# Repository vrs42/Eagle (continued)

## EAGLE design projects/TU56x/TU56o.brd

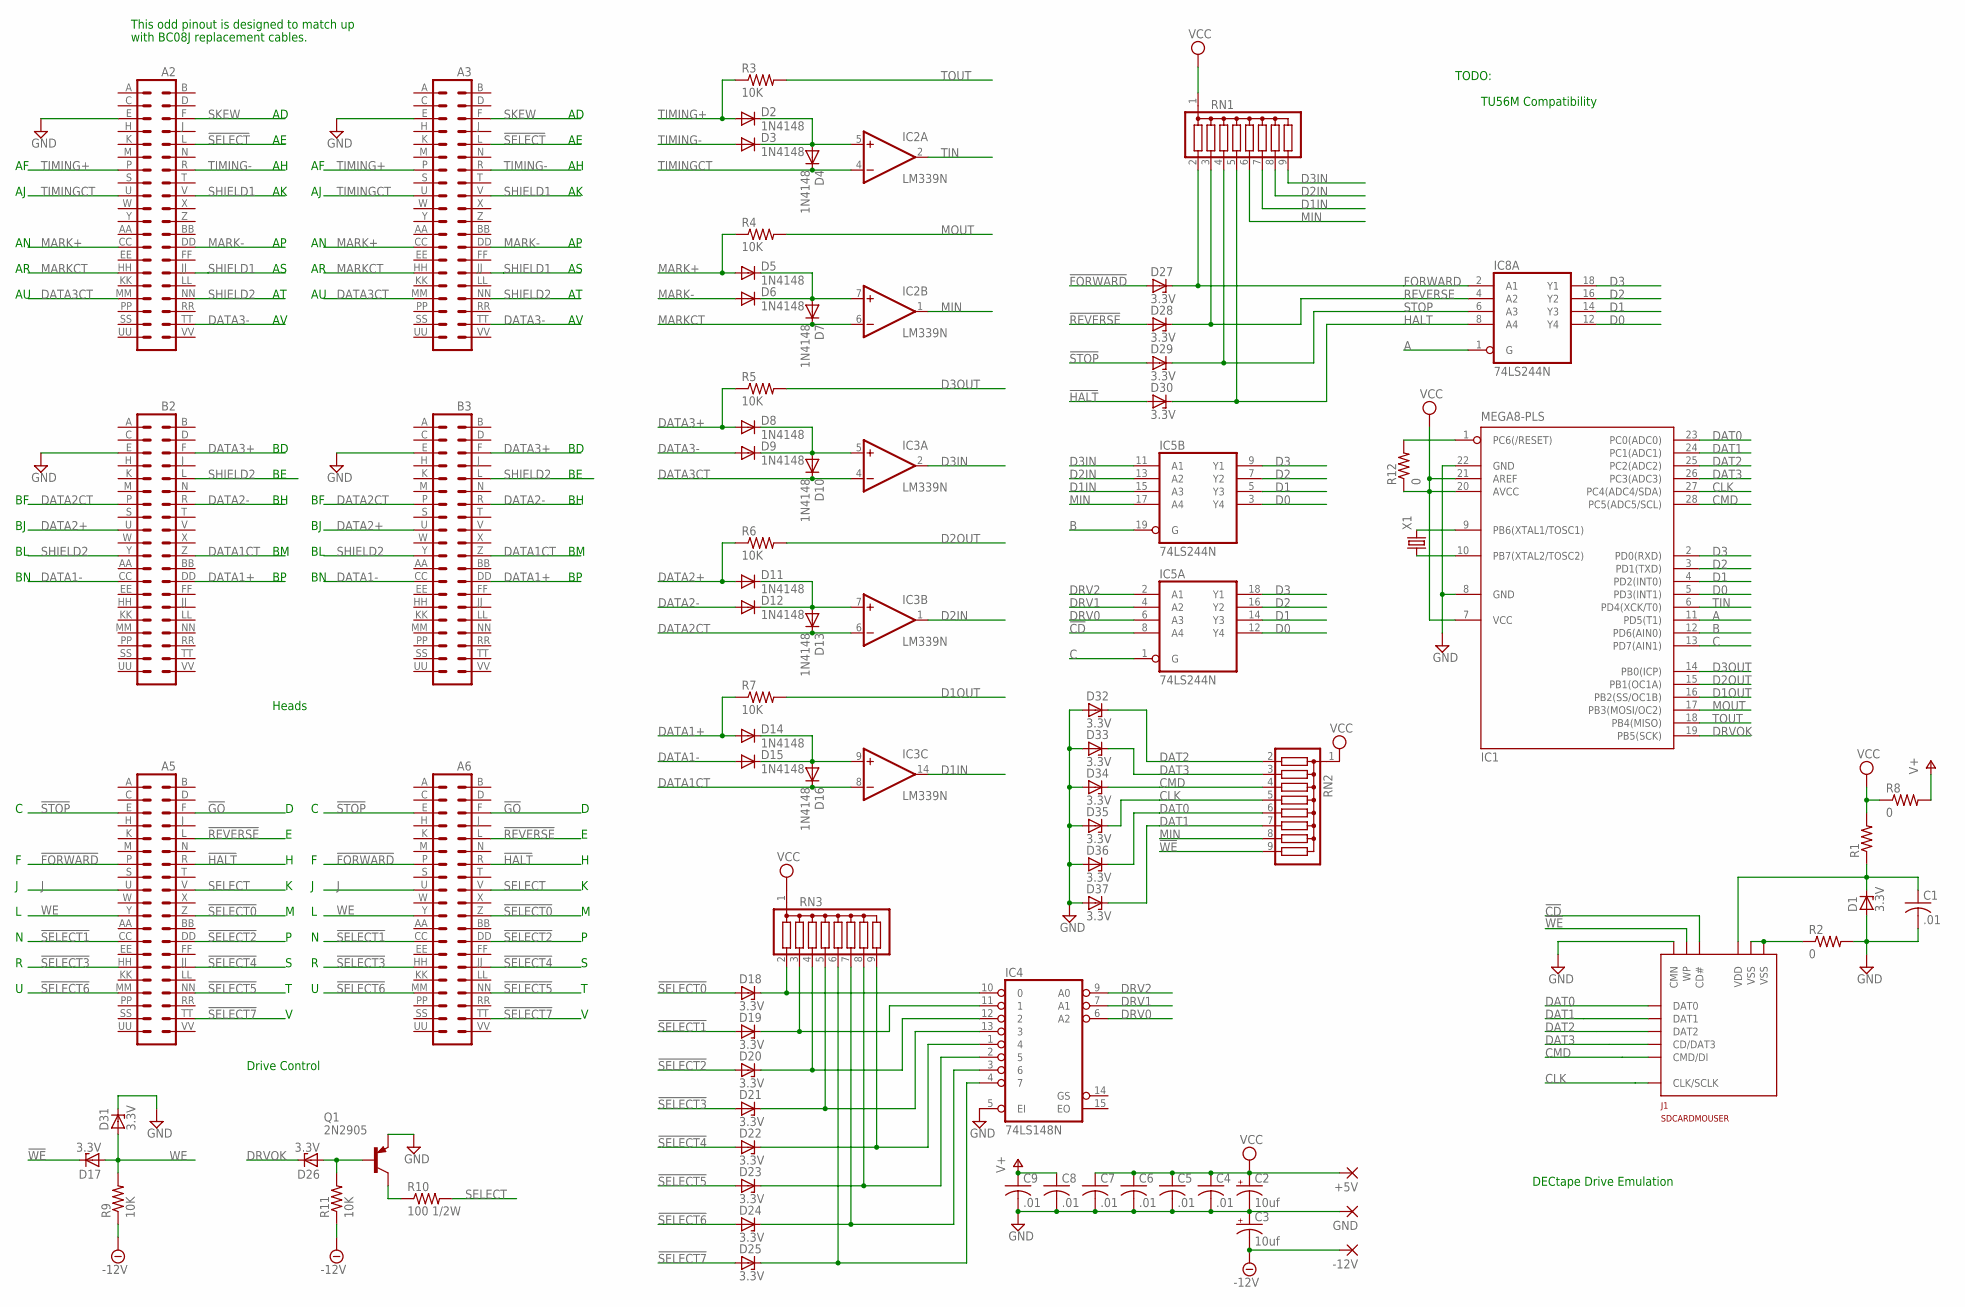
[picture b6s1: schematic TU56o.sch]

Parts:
+5V: 2,15/1,0
-12V: 2,15/1,0
A2, A3, A5, A6: DEC40PINV
B2, B3: DEC40PINV
C1, C4, C5, C6, C7, C8, C9: .01; C050-025X075
C2, C3: 10uf; E2,5-7
D1, D17, D18, D19, D20, D21, D22, D23, D24, D25, D26, D27, D28, D29, D30, D31, D32, D33, D34, D35, D36, D37: 3.3V; DO35Z10
D2, D3, D4, D5, D6, D7, D8, D9, D10, D11, D12, D13, D14, D15, D16: 1N4148; DO35-10
GND: 2,15/1,0
IC1: MEGA8-PLS; DIL28-3
IC2, IC3: LM339N; DIL14
IC4: 74LS148N; DIL16
IC5, IC8: 74LS244N; DIL20
J1: SDCARDMOUSER; SCDA1A
Q1: 2N2905; TO5
R1: R-US_0207/10; 0207/10
R2, R8, R12: 0; 0207/10
R3, R4, R5, R6, R7, R9, R11: 10K; 0207/10
R10: 100 1/2W; 0309V
RN1, RN2, RN3: G08R; SIL9
X1: CRYSTALHC49S; HC49/S

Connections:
!CD: IC5.8 (A4), J1.10 (CD#)
!FORWARD: A5.P (13), A6.P (13), D27.A
!GO: A5.F (6), A6.F (6)
!HALT: A5.R (14), A6.R (14), D30.A
!REVERSE: A5.L (10), A6.L (10), D28.A
!SELECT: A2.L (10), A3.L (10)
!SELECT0: A5.Z (22), A6.Z (22), D18.A
!SELECT1: A5.CC (25), A6.CC (25), D19.A
!SELECT2: A5.DD (26), A6.DD (26), D20.A
!SELECT3: A5.HH (29), A6.HH (29), D21.A
!SELECT4: A5.JJ (30), A6.JJ (30), D22.A
!SELECT5: A5.NN (34), A6.NN (34), D23.A
!SELECT6: A5.MM (33), A6.MM (33), D24.A
!SELECT7: A5.TT (38), A6.TT (38), D25.A
!STOP: A5.E (5), A6.E (5), D29.A
!WE: D17.C, J1.12 (WP), RN2.9
-12V: -12V.1, C3.-, R9.1, R11.1
A: IC1.11 (PD5(T1)), IC8.1 (G)
B: IC1.12 (PD6(AIN0)), IC5.19 (G)
C: IC1.13 (PD7(AIN1)), IC5.1 (G)
CLK: D35.C, IC1.27 (PC4(ADC4/SDA)), J1.5 (CLK/SCLK), RN2.5
CMD: D34.C, IC1.28 (PC5(ADC5/SCL)), J1.2 (CMD/DI), RN2.4
D0: IC1.5 (PD3(INT1)), IC5.3 (Y4), IC5.12 (Y4), IC8.12 (Y4)
D1: IC1.4 (PD2(INT0)), IC5.5 (Y3), IC5.14 (Y3), IC8.14 (Y3)
D1IN: IC3.14 (OUT), IC5.15 (A3), RN1.7
D1OUT: IC1.16 (PB2(SS/OC1B)), R7.2
D2: IC1.3 (PD1(TXD)), IC5.7 (Y2), IC5.16 (Y2), IC8.16 (Y2)
D2IN: IC3.1 (OUT), IC5.13 (A2), RN1.8
D2OUT: IC1.15 (PB1(OC1A)), R6.2
D3: IC1.2 (PD0(RXD)), IC5.9 (Y1), IC5.18 (Y1), IC8.18 (Y1)
D3IN: IC3.2 (OUT), IC5.11 (A1), RN1.9
D3OUT: IC1.14 (PB0(ICP)), R5.2
DAT0: D36.C, IC1.23 (PC0(ADC0)), J1.7 (DAT0), RN2.6
DAT1: D37.C, IC1.24 (PC1(ADC1)), J1.8 (DAT1), RN2.7
DAT2: D32.C, IC1.25 (PC2(ADC2)), J1.9 (DAT2), RN2.2
DAT3: D33.C, IC1.26 (PC3(ADC3)), J1.1 (CD/DAT3), RN2.3
DATA1+: B2.DD (26), B3.DD (26), D14.A, R7.1
DATA1-: B2.CC (25), B3.CC (25), D15.A
DATA1CT: B2.Z (22), B3.Z (22), D16.C, IC3.8 (-IN)
DATA2+: B2.U (17), B3.U (17), D11.A, R6.1
DATA2-: B2.R (14), B3.R (14), D12.A
DATA2CT: B2.P (13), B3.P (13), D13.C, IC3.6 (-IN)
DATA3+: B2.F (6), B3.F (6), D8.A, R5.1
DATA3-: A2.TT (38), A3.TT (38), D9.A
DATA3CT: A2.MM (33), A3.MM (33), D10.C, IC3.4 (-IN)
DRV0: IC4.6 (A2), IC5.6 (A3)
DRV1: IC4.7 (A1), IC5.4 (A2)
DRV2: IC4.9 (A0), IC5.2 (A1)
DRVOK: D26.C, IC1.19 (PB5(SCK))
FORWARD: D27.C, IC8.2 (A1), RN1.2
GND: A2.E (5), A3.E (5), B2.E (5), B3.E (5), C1.2, C2.-, C3.+, C4.2, C5.2, C6.2, C7.2, C8.2, C9.2, D1.A, D31.C, D32.A, D33.A, D34.A, D35.A, D36.A, D37.A, GND.1, IC1.8 (GND), IC1.22 (GND), IC2.12 (GND), IC3.12 (GND), IC4.5 (EI), IC4.8 (GND), IC5.10 (GND), IC8.10 (GND), J1.11 (CMN), J1.13 (GND), J1.14 (GND), Q1.1 (E), R2.2
HALT: D30.C, IC8.8 (A4), RN1.5
J: A5.U (17), A6.U (17)
MARK+: A2.CC (25), A3.CC (25), D5.A, R4.1
MARK-: A2.DD (26), A3.DD (26), D6.A
MARKCT: A2.HH (29), A3.HH (29), D7.C, IC2.6 (-IN)
MIN: IC2.1 (OUT), IC5.17 (A4), RN1.6, RN2.8
MOUT: IC1.17 (PB3(MOSI/OC2)), R4.2
unnamed: IC1.10 (PB7(XTAL2/TOSC2)), X1.1
unnamed: IC1.9 (PB6(XTAL1/TOSC1)), X1.2
unnamed: D18.C, IC4.10 (0), RN3.2
unnamed: D19.C, IC4.11 (1), RN3.3
unnamed: D20.C, IC4.12 (2), RN3.4
unnamed: D2.C, D3.C, D4.A, IC2.5 (+IN)
unnamed: D21.C, IC4.13 (3), RN3.5
unnamed: D22.C, IC4.1 (4), RN3.9
unnamed: D23.C, IC4.2 (5), RN3.8
unnamed: D5.C, D6.C, D7.A, IC2.7 (+IN)
unnamed: D8.C, D9.C, D10.A, IC3.5 (+IN)
unnamed: D11.C, D12.C, D13.A, IC3.7 (+IN)
unnamed: D14.C, D15.C, D16.A, IC3.9 (+IN)
unnamed: D24.C, IC4.3 (6), RN3.7
unnamed: D25.C, IC4.4 (7), RN3.6
unnamed: IC1.1 (PC6(/RESET)), R12.2
unnamed: Q1.3 (C), R10.1
unnamed: D26.A, Q1.2 (B), R11.2
REVERSE: D28.C, IC8.4 (A2), RN1.3
SELECT: A5.V (18), A6.V (18), R10.2
SHIELD1: A2.JJ (30), A2.V (18), A3.JJ (30), A3.V (18)
SHIELD2: A2.NN (34), A3.NN (34), B2.L (10), B2.Y (21), B3.L (10), B3.Y (21)
SKEW: A2.F (6), A3.F (6)
STOP: D29.C, IC8.6 (A3), RN1.4
TIMING+: A2.P (13), A3.P (13), D2.A, R3.1
TIMING-: A2.R (14), A3.R (14), D3.A
TIMINGCT: A2.U (17), A3.U (17), D4.C, IC2.4 (-IN)
TIN: IC1.6 (PD4(XCK/T0)), IC2.2 (OUT)
TOUT: IC1.18 (PB4(MISO)), R3.2
V+: C8.1, C9.1, IC2.3 (V+), IC3.3 (V+), R8.2
VCC: +5V.1, C2.+, C4.1, C5.1, C6.1, C7.1, IC1.7 (VCC), IC1.20 (AVCC), IC1.21 (AREF), IC4.16 (VCC), IC5.20 (VCC), IC8.20 (VCC), R1.2, R8.1, R12.1, RN1.1, RN2.1, RN3.1
VDD: C1.1, D1.C, J1.4 (VDD), R1.1
VSS: J1.3 (VSS), J1.6 (VSS), R2.1
WE: A5.Y (21), A6.Y (21), D17.A, D31.A, R9.2

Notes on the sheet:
Drive Control
Heads
This odd pinout is designed to match up
with BC08J replacement cables.
TODO:
TU56M Compatibility
DECtape Drive Emulation

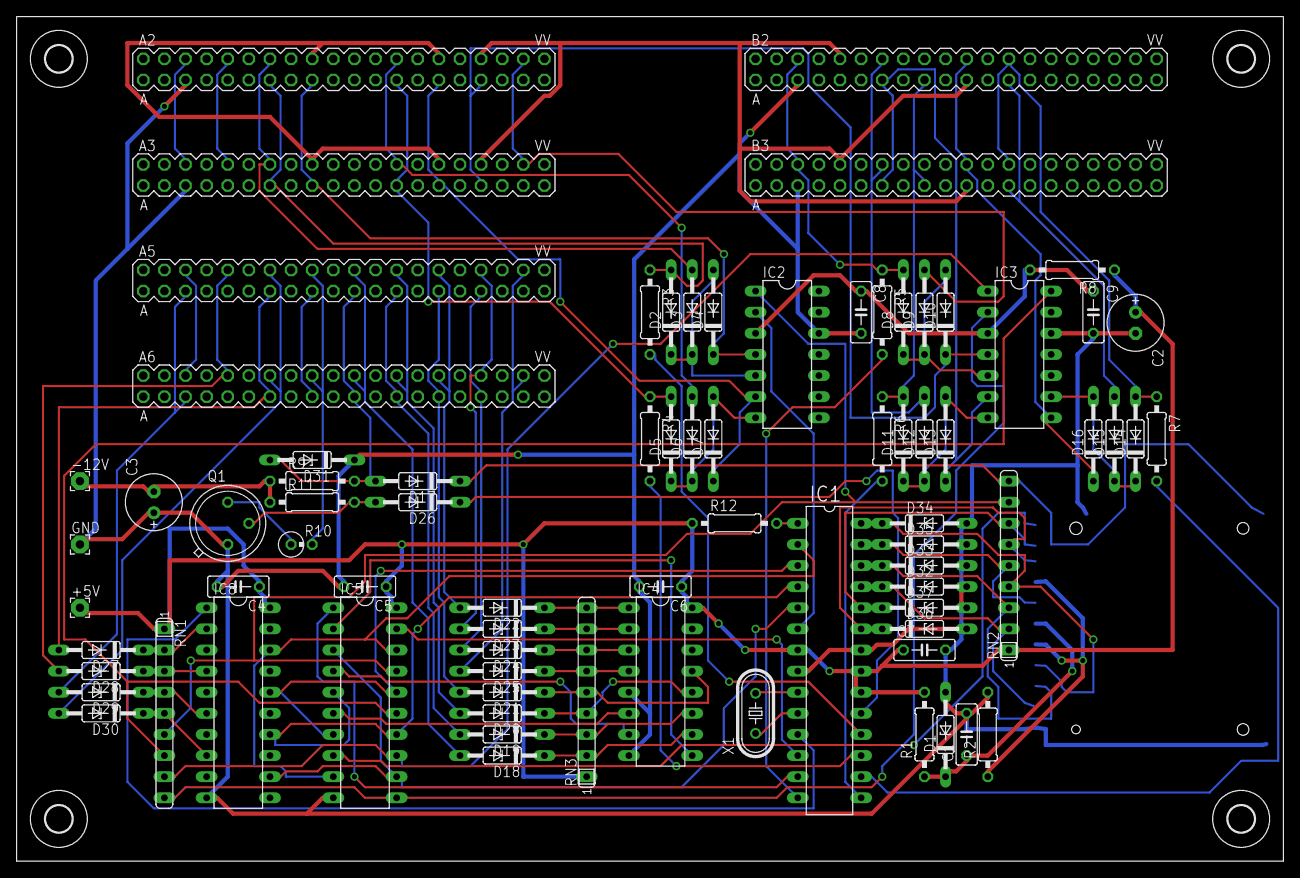
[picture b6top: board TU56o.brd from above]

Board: 2 copper layers, 152.4 x 101.6 mm, 83 parts (1 on the bottom side), 92 nets.

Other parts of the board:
U$1, U$2, U$3, U$4: 3,2
